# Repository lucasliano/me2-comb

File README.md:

<!--
*** To avoid retyping too much info. Do a search and replace for the following:
*** me2-comb, Multi-Band Combiner, project_description
-->

<!-- PROJECT LOGO -->
<br />
<p align="center">

  <h3 align="center">Multi-Band Combiner</h3>

  <p align="center">
    Final Project of ME2
    <br />
    <a href="https://github.com/lucasliano/me2-comb"><strong>Explore the docs »</strong></a>
    <br />
    <br />
    <a href="https://github.com/lucasliano/me2-comb">View Demo</a>
    ·
    <a href="https://github.com/lucasliano/me2-comb/issues">Report Bug</a>
    ·
    <a href="https://github.com/lucasliano/me2-comb/issues">Request Feature</a>
  </p>
</p>

<!-- ABOUT THE PROJECT -->
## About The Project

[![Product Name Screen Shot][pcb-3d]](https://example.com)

The objective of this project is to design, simulate, implement and measure a 5-band directional combiner. Therefore, this device must have 5 input ports and a single output. Each input will receive a 500MHz wide bandwidth signal, located at a different carrier frequency, sweeping the range between 0, 5GHz and 4, 5GHz. The output impedance shall be matched to a line impedance of 50Ω.

## Project Rationale
Quantum computing is a novel field of study within science. The aim of quantum computing is to harness some of the principles of elementary particle functioning and apply them to the area of computing. Such computers have the capacity to solve problems that would take a traditional computer decades to solve, but they do not have the capacity to solve traditional problems as efficiently, and require specific hardware to highlight the quantum phenomenology of the particles involved.

At the same time, part of the complexity inherent in this application is the design of directional couplers. These couplers are in charge of mixing different paths of the circuit, keeping the properties of the qubits associated with the process unchanged. This is why the motivation of this project is to take a first step towards the development of these technologies at a national level.

## Built With

* [CST Studio Suite](https://www.3ds.com/es/productos-y-servicios/simulia/productos/cst-studio-suite/)
* [KiCAD](https://www.kicad.org/)

<!-- CONTRIBUTING -->
## Contributing

Contributions are what make the open source community such an amazing place to be learn, inspire, and create. Any contributions you make are **greatly appreciated**.

1. Fork the Project
2. Create your Feature Branch (`git checkout -b feature/AmazingFeature`)
3. Commit your Changes (`git commit -m 'Add some AmazingFeature'`)
4. Push to the Branch (`git push origin feature/AmazingFeature`)
5. Open a Pull Request

<!-- LICENSE -->
## License

Distributed under the MIT License. See `LICENSE` for more information.

<!-- CONTACT -->
## Contact

Lucas Liaño - lliano@frba.utn.edu.ar

Manuel Dieguez - madieguez@frba.utn.edu.ar

Juan Costa Suarez - jcostasurez@frba.utn.edu.ar

Project Link: [https://github.com/lucasliano/me2-comb](https://github.com/lucasliano/me2-comb)

<!-- MARKDOWN LINKS & IMAGES -->
<!-- https://www.markdownguide.org/basic-syntax/#reference-style-links -->
[product-screenshot]: images/screenshot.png
[pcb-screenshot]: images/PCB_3d.png
[pcb-3d]: images/PCB_3d.png

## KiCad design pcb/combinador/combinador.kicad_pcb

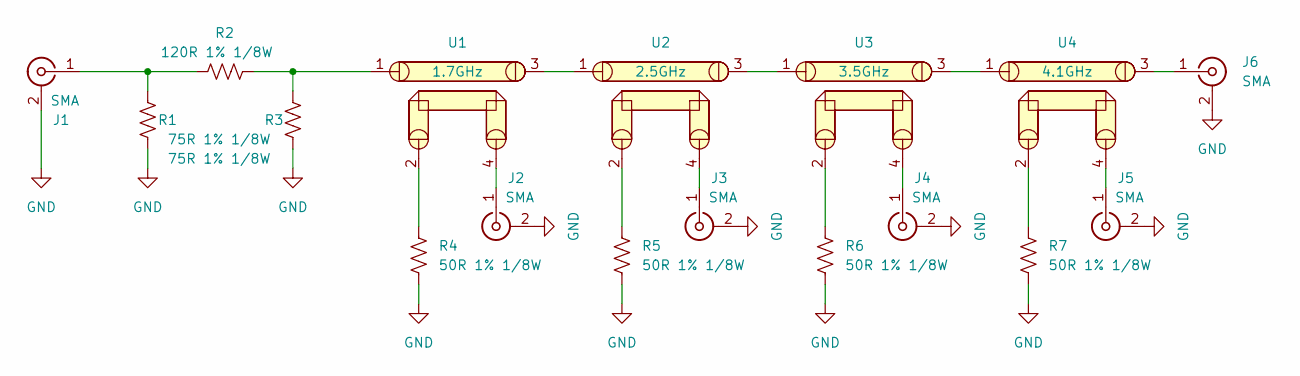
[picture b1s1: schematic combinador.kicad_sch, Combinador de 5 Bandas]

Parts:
J1, J2, J3, J4, J5, J6: SMA; SMA_horizontal_microstrip
R1, R3: 75R 1% 1/8W; R_0603
R2: 120R 1% 1/8W; R_0603
R4, R5, R6, R7: 50R 1% 1/8W; R_0603
U1: 1.7GHz; comb_1.7GHz
U2: 2.5GHz; comb_2.5GHz
U3: 3.5GHz; comb_3.5GHz
U4: 4.1GHz; comb_4.1GHz

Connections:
GND: J1.2 (Ext), J2.2 (Ext), J3.2 (Ext), J4.2 (Ext), J5.2 (Ext), J6.2 (Ext), R1.2, R3.2, R4.2, R5.2, R6.2, R7.2
unnamed: J1.1 (In), R1.1, R2.1
unnamed: J2.1 (In), U1.4
unnamed: J3.1 (In), U2.4
unnamed: J4.1 (In), U3.4
unnamed: J5.1 (In), U4.4
unnamed: J6.1 (In), U4.3
unnamed: R2.2, R3.1, U1.1
unnamed: R4.1, U1.2
unnamed: R5.1, U2.2
unnamed: R6.1, U3.2
unnamed: R7.1, U4.2
unnamed: U1.3, U2.1
unnamed: U2.3, U3.1
unnamed: U3.3, U4.1

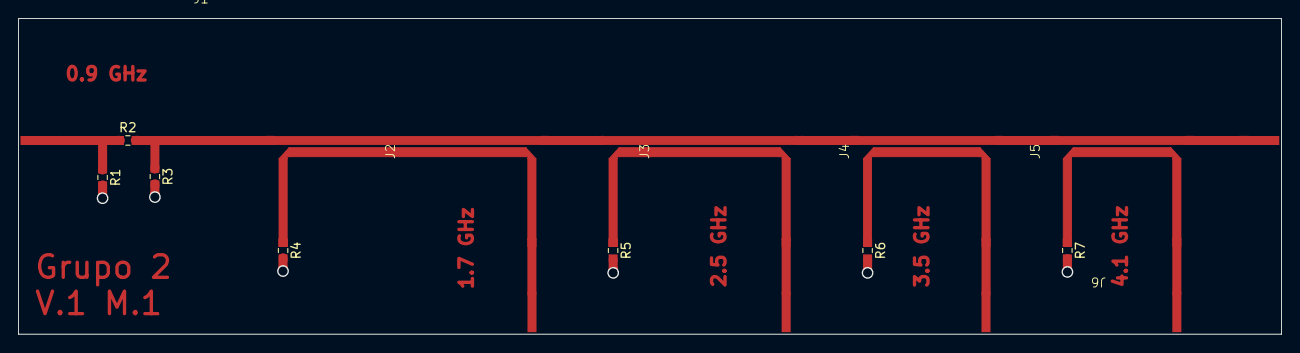
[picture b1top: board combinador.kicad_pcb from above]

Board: 2 copper layers, 140.0 x 35.0 mm, 17 parts (0 on the bottom side), 15 nets.

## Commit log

2023-10-14 First Commit w/ simple layout
2023-10-14 Updating readme
2023-10-25 Actualización
    Agregado de modelo 3d de conectores, correxión en la medida de los pads de los resistores. Agregado de etiquetas de cada acoplador.
2023-10-26 Readme changes
    Adding new images to the documentation
2023-10-26 Actualización
    Cambio de etiquetas de conectores
